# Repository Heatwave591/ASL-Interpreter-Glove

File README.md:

**Project Goals:**
* Design an American Sign Language (ASL) interpreting glove that converts sign language to English and outputs the translation.
* Recognize and translate the entire ASL alphabet.
* Identify and process basic static signs.
* Design a PCB for the circuit.

**Necessary Equipment and Sensors:**
* [ESP32 microcontroller x 2](https://www.amazon.com/HiLetgo-ESP-WROOM-32-Development-Microcontroller-Integrated/dp/B0718T232Z/ref=sr_1_1?crid=1E77MJF3QUDXL&dib=eyJ2IjoiMSJ9.soccUwva0RJIrxBgE16WUjGVb2gBzEZbRkcOjXFbl7txw_m8j2eB6sRBQfng_1By2xLbPOThXIIX6mm44zSRKBxo3DmCSaaPxRREeTvaz6mRqJSFdvX0UV4u7YCUFF9VzJMH5HSEm69ay5sR7vqI16iSSKkc1n5M4U171zWHULnC6If07JvZlS_vyRk9eYY7LQVSKsYTOywvE9E0JswhrlGnK3uilLnHBdO0v0LSaLqrTVmNWqHisUFKCX0RmKDC_S3Y7NVDhJZNNPbb7mO3_IXQbJ1bYXfzatGhKCRAPVQ.BtD1TH4fLNusaAd__wgz_MqSrZH6kXXjVtp4MKl7kw4&dib_tag=se&keywords=ESP32+adafruit&qid=1745643407&s=industrial&sprefix=esp32+adafruit%2Cindustrial%2C97&sr=1-1)
* [Flex sensors x 15](https://www.amazon.com/dp/B00LP25V1A?ref=ppx_yo2ov_dt_b_fed_asin_title&th=1)
* [MPU6050 x 2](https://www.amazon.com/dp/B0BLGT1F5F?ref=ppx_yo2ov_dt_b_fed_asin_title)
* [Pair of gloves x 1](https://www.amazon.com/Cotton-Gloves-Handling-Inspection-Photography/dp/B07ZMXNCQ5/ref=sr_1_1_sspa?crid=38A9OGK836FWP&dib=eyJ2IjoiMSJ9.RmDXSiT6_NwJIY7lLORg_hXRWdsfz5oneae0ttufA6xlE6yOU3XQI5IIw6CIP2ooXhPPXH6yb202yVkcDbKFN4tPhf6yFDZhMkIwZQfw2T55du-INUa5a1qSomWbeLcX6CZY6OHX3BhG44cjwEK9NmnZh7daNdz0VL7yuGMPpklnTagvLmJEJSSrEW2Hh6p0hE0ZwRGx5XYDeJZQDgXf2UWIse_s8L0uHNks6Kb9-btsYlCjnz9PRu4FuRj5JpmsLnc2chX2WcwSZNavxAectru4EzFSM2AwrvvHo5iIlK4.F7i_RE5KeiKyVe0g_Vekxm2Gx2jjtA3lpxnY2aW0wPw&dib_tag=se&keywords=gloves%2Bcotton&qid=1745643483&sprefix=gloves%2Bcotton%2Caps%2C123&sr=8-1-spons&sp_csd=d2lkZ2V0TmFtZT1zcF9hdGY&th=1)

  Note - The links for the products are embedded in the text. Clicking the link will redirect you to amazon.com.

# Project Description
The ASL-interpreting glove will be designed to detect hand gestures and translate them into spoken words and a visual interface output. The system will consist of flex sensors to track finger movements, MPU6050 sensors for motion detection, and ESP32 microcontrollers to process and transmit data to an output system.

# System Setup
### Hardware
- The hardware consists of five flex sensors and an IMU in each hand
- The flex sensors need to be connected to the analog pins of the ESP32. Make sure to choose the correct pins according to your circuit.
	- All the ESP32 models do not have analog pins. If that happens, check the datasheet of the ESP32 and use the ADC pins instead and you should be good to go.
	- Many ESP32 boards have the issue of some pins being rendered useless when the wifi module is on. If the pin that is needed is being used by wifi, then, you have no choice other than using a different pin.
	
- The flex sensors need to create a conventional voltage divider circuit with the same value of resistors across all sensors (We have used the 10KOhm Resistor).
- The IMU follows a straight forward serial connection. 
	- Connect the power rails together
	- Connect the Serial Clock and the Serial Data of the IMU to the Serial Clock and Serial Data of the ESP32 respectively
- This concludes the hardware setup of the glove.

### Software 
The software consists of 4 parts.
- Arduino IDE Setup
- Firebase Setup
- Arduino Execution 
- HTML Setup and Execution

#### Arduino IDE Setup
- Download the Arduino IDE.
- Open the IDE.
- To make the ESP32 compatable, go to File > Preferences
- Paste this link in the Additional Board Manager URL's box
	- "https://raw.githubusercontent.com/espressif/arduino-esp32/gh-pages/package_esp32_index.json"
- Restart the IDE
- Go to Boards Manager and download the ESP32 package.
- Install the following libraries.
	- WiFi.h
	- Firebase_ESP_Client.h
	- Adafruit mpu6050
	- Adafruit Unified Sensor
	- Adafruit BusIO

- We will be using 2 scripts in this approach, but technically, there are many scripts in the repository that follow different methods that result in the same results.
- The process that we followed for this project is to essentially fetch data from the sensors, package the data into a JSON file, send it to a Firebase server and have the HTML file scrap data from there.

#### Firebase Setup
- Open Firebase in your browser.
- Login using your Google account.
- Go to Console.
- Create a new Firebase Project.
- Name your Project whatever you want. We have called it "ASL-Interpreter-Glove"
- Follow the instruction on screen and create the project.
- Enter the project.
- In the right side, Navigate to Product Categories > Build > Realtime Database.
- This is where our data will be seen.
- The link that is seen on top is our "DATABASE_URL". We will need this.
- Go to the project settings on the top right corner of the page.
- We will need the "API_KEY".
- This concludes the firebase setup. Missing out on any of these steps will result in the code not working.

#### Arduino Execution
- Open up the Arduino Editor.
- Since we have 2 gloves, we will have to upload and run 2 different codes on 2 ESP32s. But first, some modifications must be made to the code so that it will be compatible with the computer and the server.
- The changes are the same for both the codes.
- Set up the wifi network in the code
	- I have put placeholder values for the SSID and passwords for safety. This needs to be changed prior to running.
	- Replace WIFI_SSID and WIFI_PASSWORD with your credentials. Make sure that the network is in the 2.4GHz band 
	- Replace API_KEY and DATABASE_URL with the information we got from the firebase server.
- Once all of this is done, the code is ready to be dumped in the ESP32
- For the left hand and up and load [Firebase_Flex_Left.ino](Firebase%20Stuff/Firebase_Flex_Right/Firebase_Flex_Right.ino)
- Do the same with [Firebase_Flex_Right.ino](Firebase%20Stuff/Firebase_Flex_Right/Firebase_Flex_Right.ino) for the ESP32 that goes on the Right hand.

#### HTML Setup and Execution
- Once the server is up and running, We will have to setup the webpage where the inferences will be shown.
- Download the [webserver.html](webserver.html) file.
- Make the changes in lines 192, 193, 194 with the API_KEY, DATABASE_URL and PROJECT_ID.
- Now, host the file with python. (Note that you will not need a separate python script to do this. It can be done in the python interactive terminal by following these setps)
	- Go to the file directory and open a python interactive terminal.
	- Run this code  ``` python3 -m SimpleHTTPServer 3000```
	- This will locally host the webpage.
	- Open the web browser and type ```localhost:3000 ```
	- The port used here is 3000, this can be changed to any other port too.

# Machine Learning Model Interpretation
- The machine learning model runs by taking data out of the serial ports.
- When the ESP32 is executing the code, close all the serial monitors and then run the python sctript [INT_model_inference.py](Interpretation/INT_model_inference.py).
- This will run the machine learning model and send inferences to the webpage.

# Possible Future Works
* Support for dynamic signs.
* Integration of two gloves for improved accuracy.

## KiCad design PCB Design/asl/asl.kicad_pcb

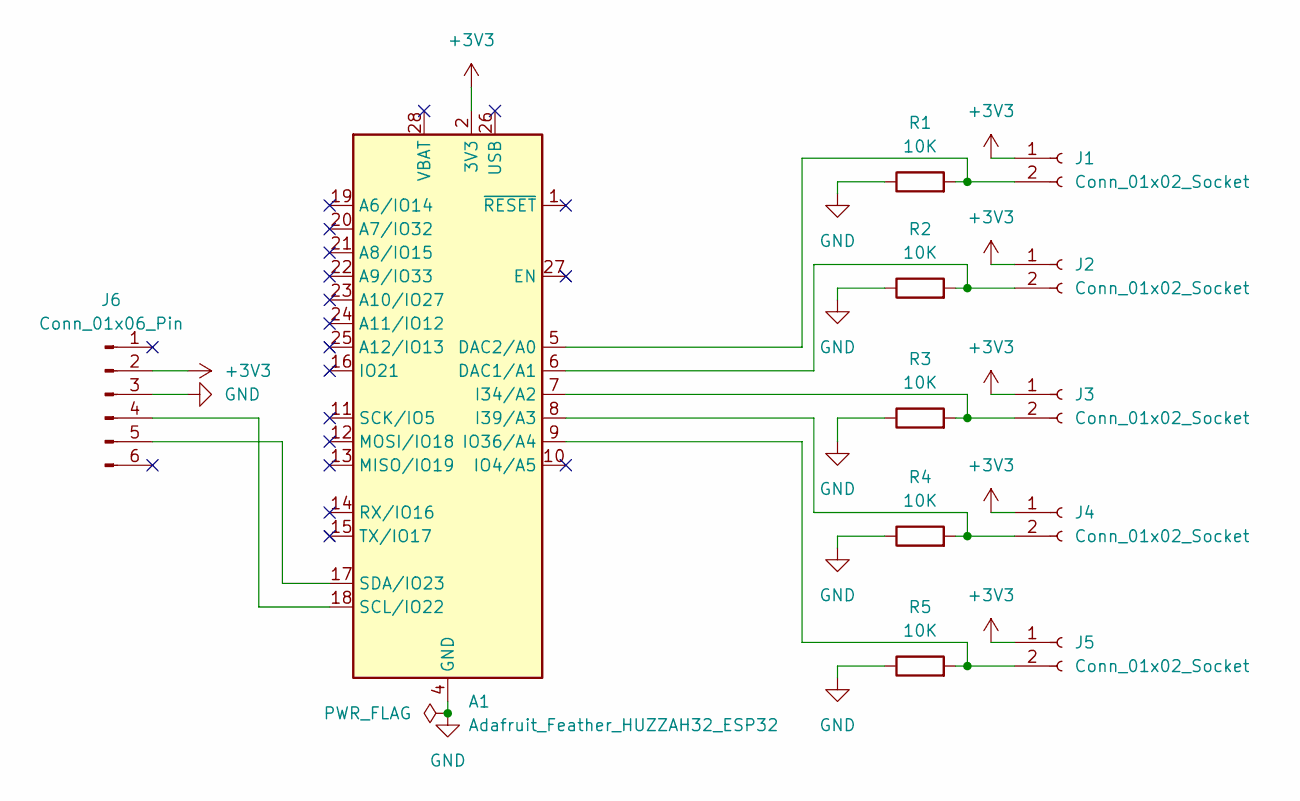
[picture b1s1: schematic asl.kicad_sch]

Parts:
A1: Adafruit_Feather_HUZZAH32_ESP32; Adafruit_Feather
J1, J2, J3, J4, J5: Conn_01x02_Socket; TerminalBlock_bornier-2_P5.08mm
J6: Conn_01x06_Pin; PinSocket_1x06_P2.54mm_Vertical
R1, R2, R3, R4, R5: 10K; R_Axial_DIN0207_L6.3mm_D2.5mm_P7.62mm_Horizontal

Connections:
+3V3: A1.2 (3V3), J1.1, J2.1, J3.1, J4.1, J5.1, J6.2
GND: A1.4 (GND), J6.3, R1.1, R2.1, R3.1, R4.1, R5.1
unnamed: A1.6 (DAC1/A1), J2.2, R2.2
unnamed: A1.5 (DAC2/A0), J1.2, R1.2
unnamed: A1.7 (I34/A2), J3.2, R3.2
unnamed: A1.8 (I39/A3), J4.2, R4.2
unnamed: A1.9 (IO36/A4), J5.2, R5.2
unnamed: A1.18 (SCL/IO22), J6.4
unnamed: A1.17 (SDA/IO23), J6.5

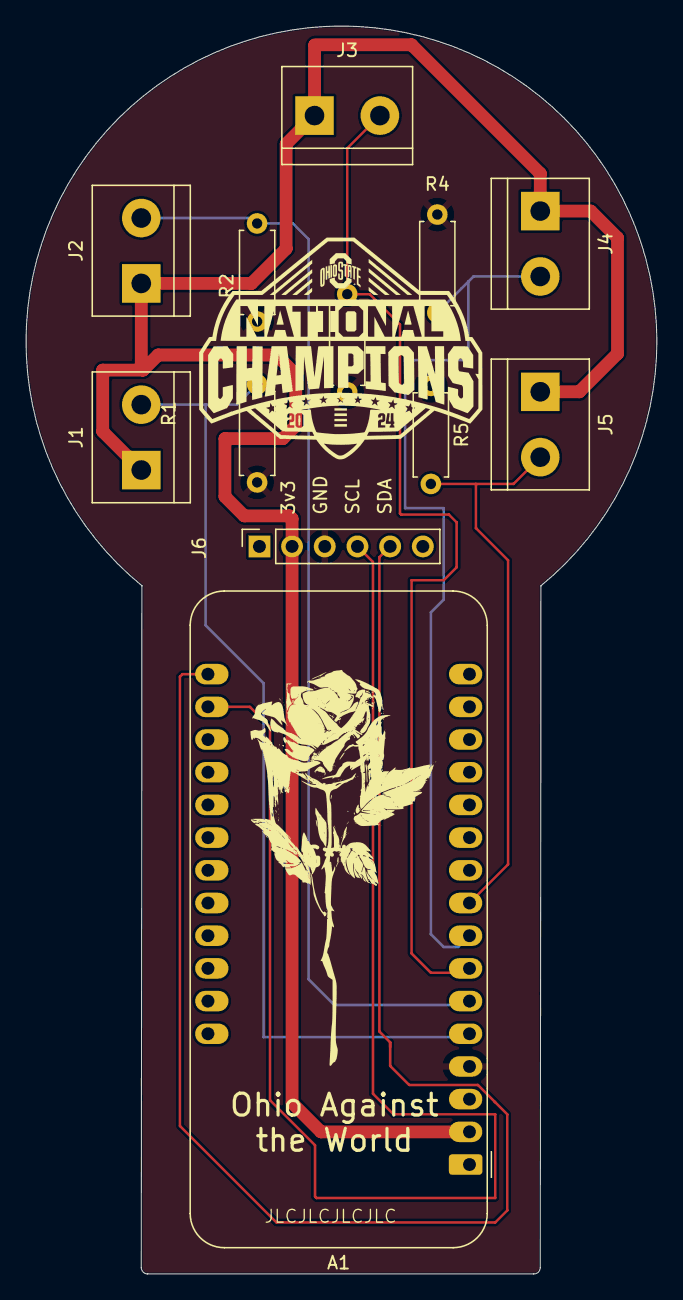
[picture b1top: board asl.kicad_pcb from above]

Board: 2 copper layers, 49.0 x 97.0 mm, 12 parts (0 on the bottom side), 9 nets.

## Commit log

2025-02-05 Readme modified
2025-02-05 readme updated
2025-02-26 update flex_sensor: 5 sensors
2025-03-03 randomization
2025-03-03 relocation
2025-03-03 SPIFFS base webpage attempt 1
2025-03-03 modify webpage
2025-03-03 SPIFFS file management test
2025-03-03 webpage fixed
2025-03-03 create webserver_SPIFFS and flex
2025-03-15 firebase testing
2025-03-15 CREATE Firebase Random Array
2025-03-15 CREATE Firebase_Flex
2025-03-15 code cleanup
2025-03-16 UPDATE Firebase_Flex with LEFT
2025-03-16 cleanup
2025-03-16 CREATE Firebase_Flex_Right
2025-03-16 update firebase right
2025-03-16 update firebase left
2025-03-17 Random Forest Decision model- First Commit
2025-03-17 Added gyro to firebase right
2025-03-17 MPU6050 update for firebase left
2025-03-18 CREATE capture1
2025-03-18 Tested Interpreter Code: Prediction mode not working
2025-03-18 webpage changes
2025-03-24 CREATE Submissions
2025-03-31 Create PCB Schematic and Layout
2025-03-31 Added CSVs for 10 datasets of 10 values each
2025-04-01 Added 10 more samples per dataset
2025-04-01 Interpreter Model + Data Collection
2025-04-01 ML model testing
2025-04-01 Compiled datasets
2025-04-04 added more letters
2025-04-07 UPLOAD PCB Files
2025-04-09 Right hand predictions added
2025-04-09 Added inferences for left hand
2025-04-09 Firebase and SPIFFS with prediction
2025-04-10 Model Testing + Final Datasets
2025-04-11 added some signs
2025-04-12 Final edit
2025-04-13 submissions final
2025-04-25 Security enhancements
2025-04-25 Update README.md
    changes 1KOhm resistor to 10KOhm resistor
2025-08-28 README edits
